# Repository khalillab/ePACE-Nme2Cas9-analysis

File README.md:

# ePACE-Nme2Cas9-analysis
Scripts used for analysis in the Nme2Cas9 evolution project.

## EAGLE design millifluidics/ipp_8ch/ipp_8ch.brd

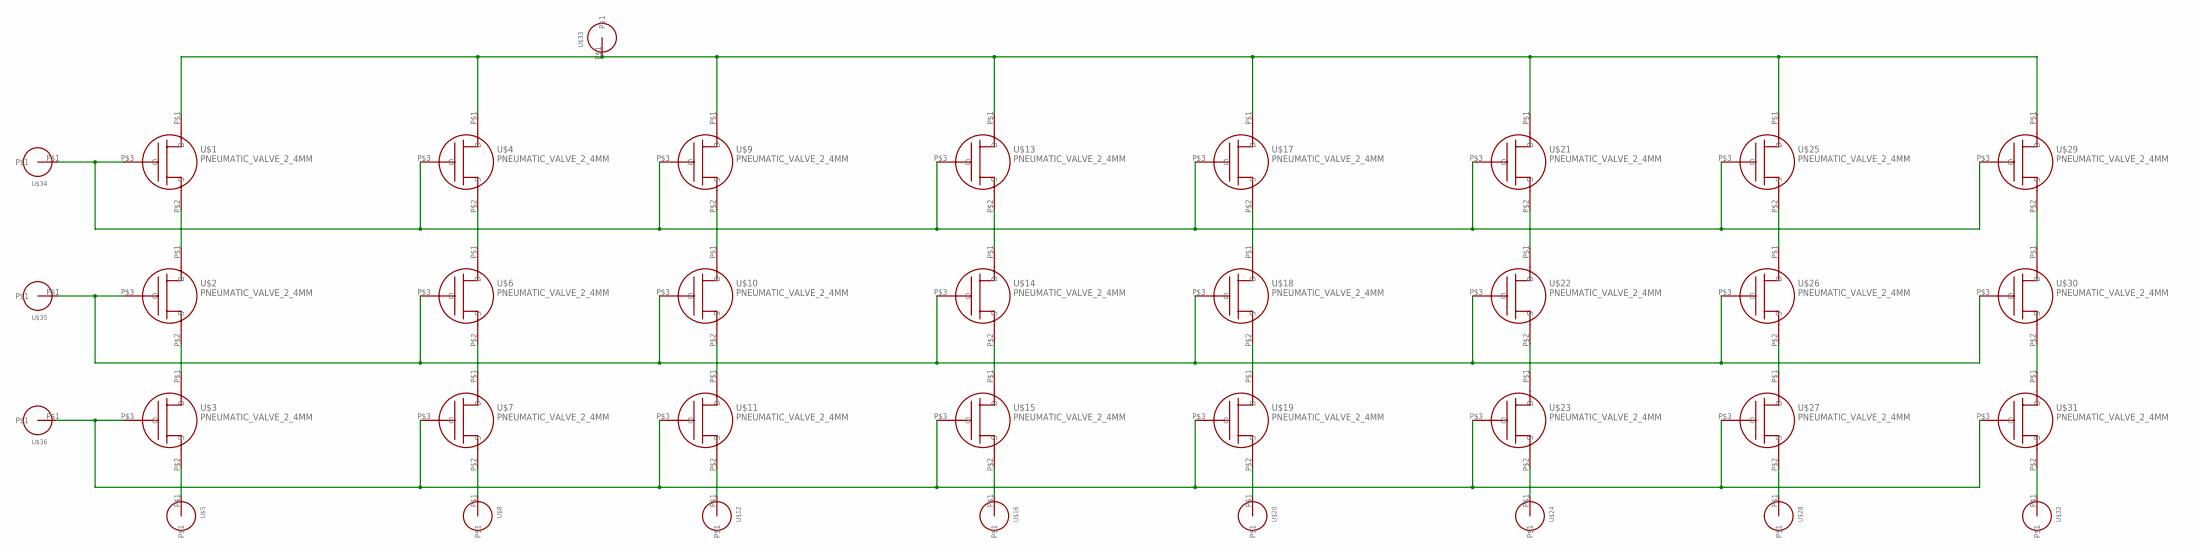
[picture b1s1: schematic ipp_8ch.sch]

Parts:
U$1, U$2, U$3, U$4, U$6, U$7, U$9, U$10, U$11, U$13, U$14, U$15, U$17, U$18, U$19, U$21, U$22, U$23, U$25, U$26, U$27, U$29, U$30, U$31: PNEUMATIC_VALVE_2_4MM; 2_4MM_PNEUMATIC_VALVE_C5_F4
U$5, U$8, U$12, U$16, U$20, U$24, U$28, U$32, U$33, U$34, U$35, U$36: 10-32_BARBED_CONNECTOR

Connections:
unnamed: U$1.P$2 (S), U$2.P$1 (D)
unnamed: U$2.P$2 (S), U$3.P$1 (D)
unnamed: U$4.P$2 (S), U$6.P$1 (D)
unnamed: U$3.P$2 (S), U$5.P$1
unnamed: U$6.P$2 (S), U$7.P$1 (D)
unnamed: U$7.P$2 (S), U$8.P$1
unnamed: U$9.P$2 (S), U$10.P$1 (D)
unnamed: U$10.P$2 (S), U$11.P$1 (D)
unnamed: U$11.P$2 (S), U$12.P$1
unnamed: U$13.P$2 (S), U$14.P$1 (D)
unnamed: U$14.P$2 (S), U$15.P$1 (D)
unnamed: U$15.P$2 (S), U$16.P$1
unnamed: U$17.P$2 (S), U$18.P$1 (D)
unnamed: U$18.P$2 (S), U$19.P$1 (D)
unnamed: U$19.P$2 (S), U$20.P$1
unnamed: U$21.P$2 (S), U$22.P$1 (D)
unnamed: U$22.P$2 (S), U$23.P$1 (D)
unnamed: U$23.P$2 (S), U$24.P$1
unnamed: U$25.P$2 (S), U$26.P$1 (D)
unnamed: U$26.P$2 (S), U$27.P$1 (D)
unnamed: U$27.P$2 (S), U$28.P$1
unnamed: U$29.P$2 (S), U$30.P$1 (D)
unnamed: U$30.P$2 (S), U$31.P$1 (D)
unnamed: U$31.P$2 (S), U$32.P$1
unnamed: U$1.P$1 (D), U$4.P$1 (D), U$9.P$1 (D), U$13.P$1 (D), U$17.P$1 (D), U$21.P$1 (D), U$25.P$1 (D), U$29.P$1 (D), U$33.P$1
unnamed: U$1.P$3 (G), U$4.P$3 (G), U$9.P$3 (G), U$13.P$3 (G), U$17.P$3 (G), U$21.P$3 (G), U$25.P$3 (G), U$29.P$3 (G), U$34.P$1
unnamed: U$2.P$3 (G), U$6.P$3 (G), U$10.P$3 (G), U$14.P$3 (G), U$18.P$3 (G), U$22.P$3 (G), U$26.P$3 (G), U$30.P$3 (G), U$35.P$1
unnamed: U$3.P$3 (G), U$7.P$3 (G), U$11.P$3 (G), U$15.P$3 (G), U$19.P$3 (G), U$23.P$3 (G), U$27.P$3 (G), U$31.P$3 (G), U$36.P$1

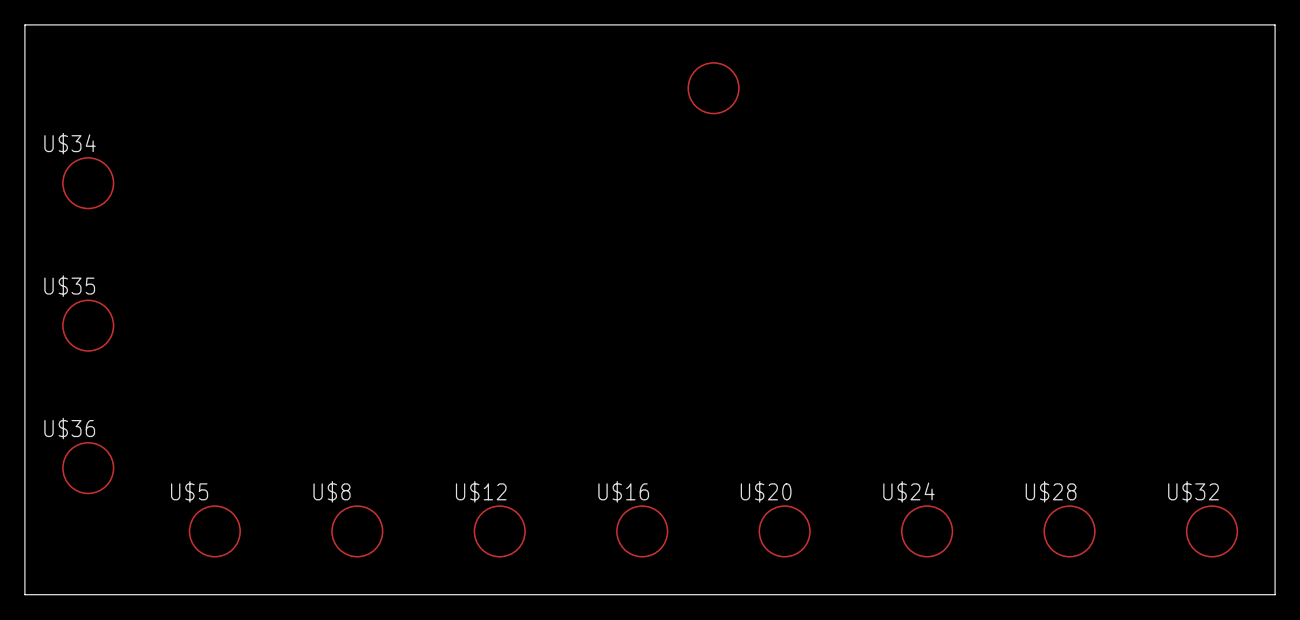
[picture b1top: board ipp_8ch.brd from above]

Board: 16 copper layers, 100.3 x 45.7 mm, 36 parts (0 on the bottom side), 28 nets.

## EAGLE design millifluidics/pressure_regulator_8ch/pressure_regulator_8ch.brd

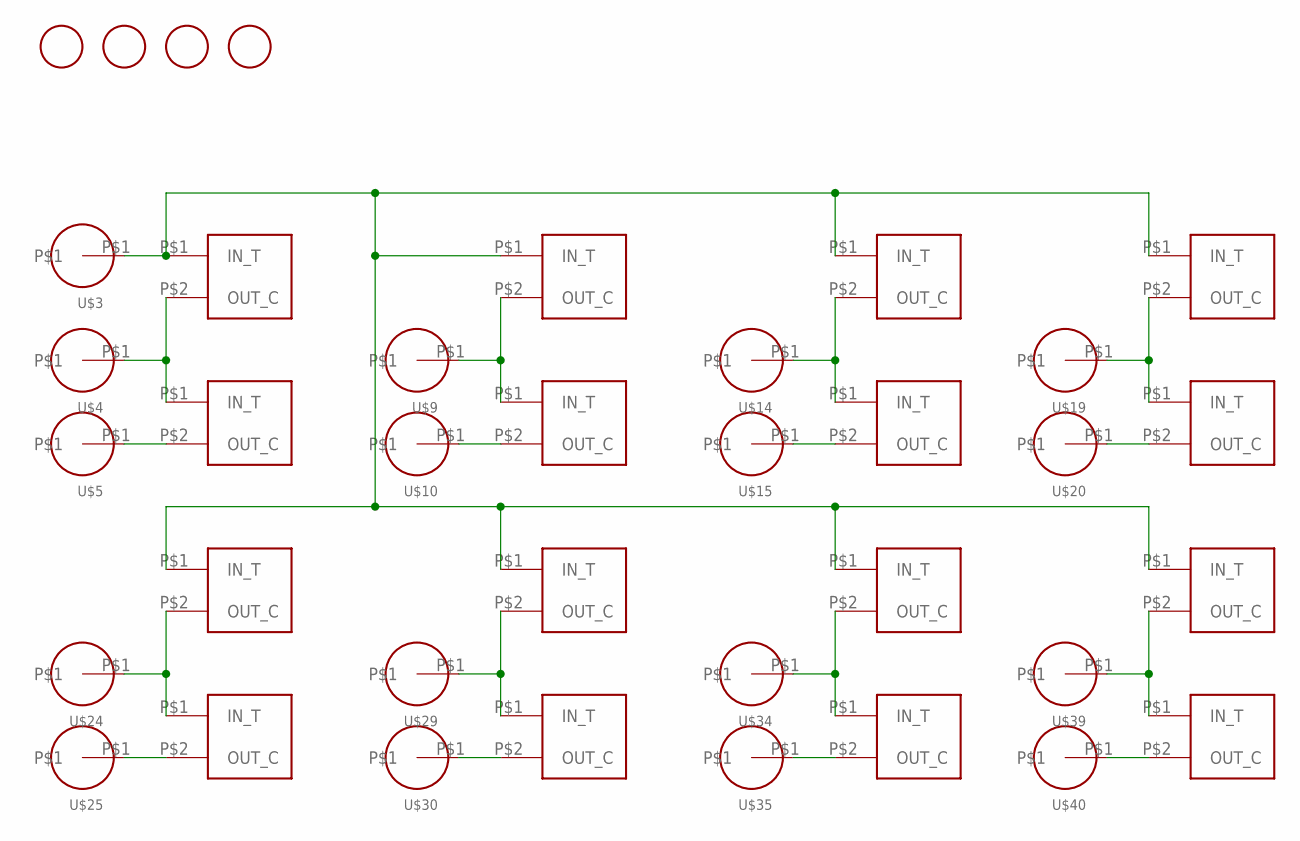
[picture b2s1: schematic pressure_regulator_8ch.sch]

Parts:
U$1, U$2, U$6, U$7, U$11, U$12, U$16, U$17, U$21, U$22, U$26, U$27, U$31, U$32, U$36, U$37: PARKER_PROP_VALVE
U$3, U$4, U$5, U$9, U$10, U$14, U$15, U$19, U$20, U$24, U$25, U$29, U$30, U$34, U$35, U$39, U$40: 10-32_BARBED_CONNECTOR
U$50, U$51, U$52, U$53: M4

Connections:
unnamed: U$2.P$2 (OUT_C), U$5.P$1
unnamed: U$1.P$2 (OUT_C), U$2.P$1 (IN_T), U$4.P$1
unnamed: U$1.P$1 (IN_T), U$3.P$1, U$6.P$1 (IN_T), U$11.P$1 (IN_T), U$16.P$1 (IN_T), U$21.P$1 (IN_T), U$26.P$1 (IN_T), U$31.P$1 (IN_T), U$36.P$1 (IN_T)
unnamed: U$7.P$2 (OUT_C), U$10.P$1
unnamed: U$6.P$2 (OUT_C), U$7.P$1 (IN_T), U$9.P$1
unnamed: U$12.P$2 (OUT_C), U$15.P$1
unnamed: U$11.P$2 (OUT_C), U$12.P$1 (IN_T), U$14.P$1
unnamed: U$17.P$2 (OUT_C), U$20.P$1
unnamed: U$16.P$2 (OUT_C), U$17.P$1 (IN_T), U$19.P$1
unnamed: U$22.P$2 (OUT_C), U$25.P$1
unnamed: U$21.P$2 (OUT_C), U$22.P$1 (IN_T), U$24.P$1
unnamed: U$27.P$2 (OUT_C), U$30.P$1
unnamed: U$26.P$2 (OUT_C), U$27.P$1 (IN_T), U$29.P$1
unnamed: U$32.P$2 (OUT_C), U$35.P$1
unnamed: U$31.P$2 (OUT_C), U$32.P$1 (IN_T), U$34.P$1
unnamed: U$37.P$2 (OUT_C), U$40.P$1
unnamed: U$36.P$2 (OUT_C), U$37.P$1 (IN_T), U$39.P$1

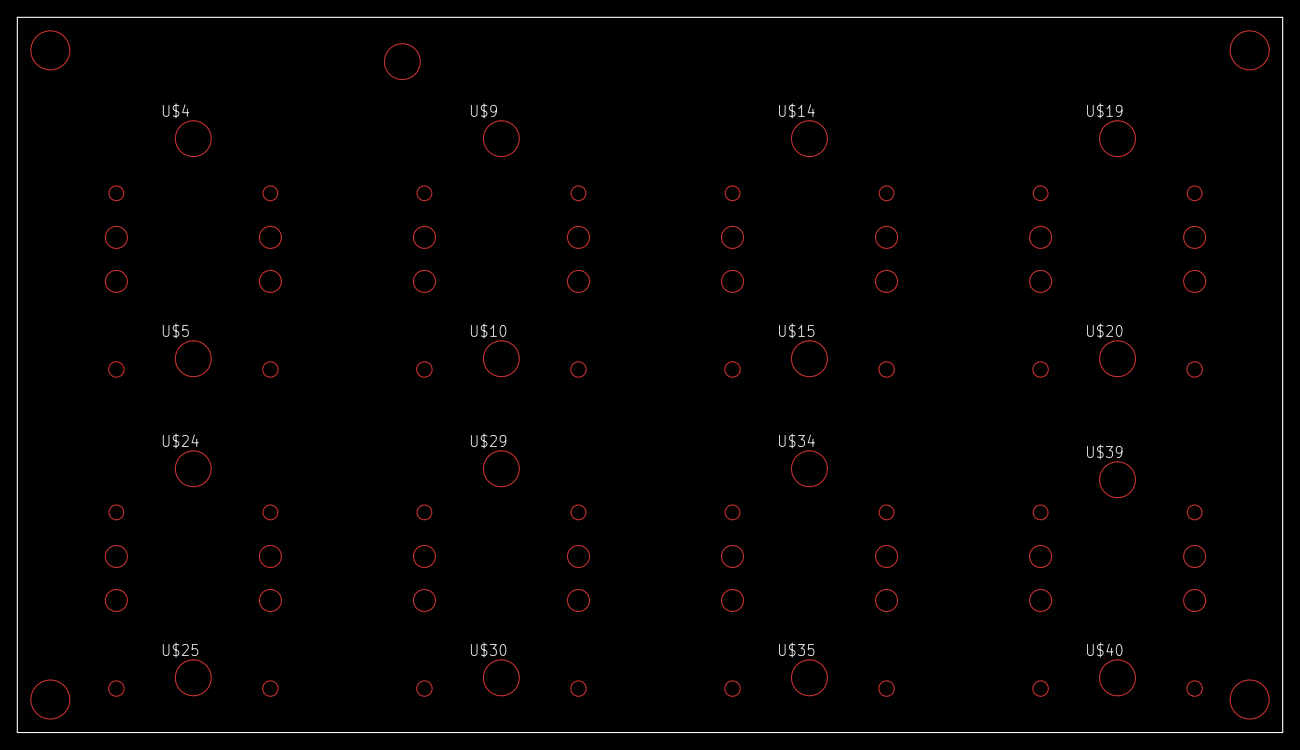
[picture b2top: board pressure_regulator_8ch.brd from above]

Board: 16 copper layers, 146.1 x 82.5 mm, 37 parts (0 on the bottom side), 17 nets.

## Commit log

2022-01-04 Adding files
2022-01-10 Adding protospacer offtarget scripts
2022-01-10 Adding eVOLVER DPU code
2022-01-10 Adding data
2022-01-24 Adding millifluidic designs
